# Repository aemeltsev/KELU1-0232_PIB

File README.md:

# KELU1-0232_PIB

![PCB image][KELU1-0232_PIB]

[KELU1-0232_PIB]:https://raw.githubusercontent.com/aemeltsev/KELU1-0232_PIB/master/hw/KELU1-0232_PCB.png

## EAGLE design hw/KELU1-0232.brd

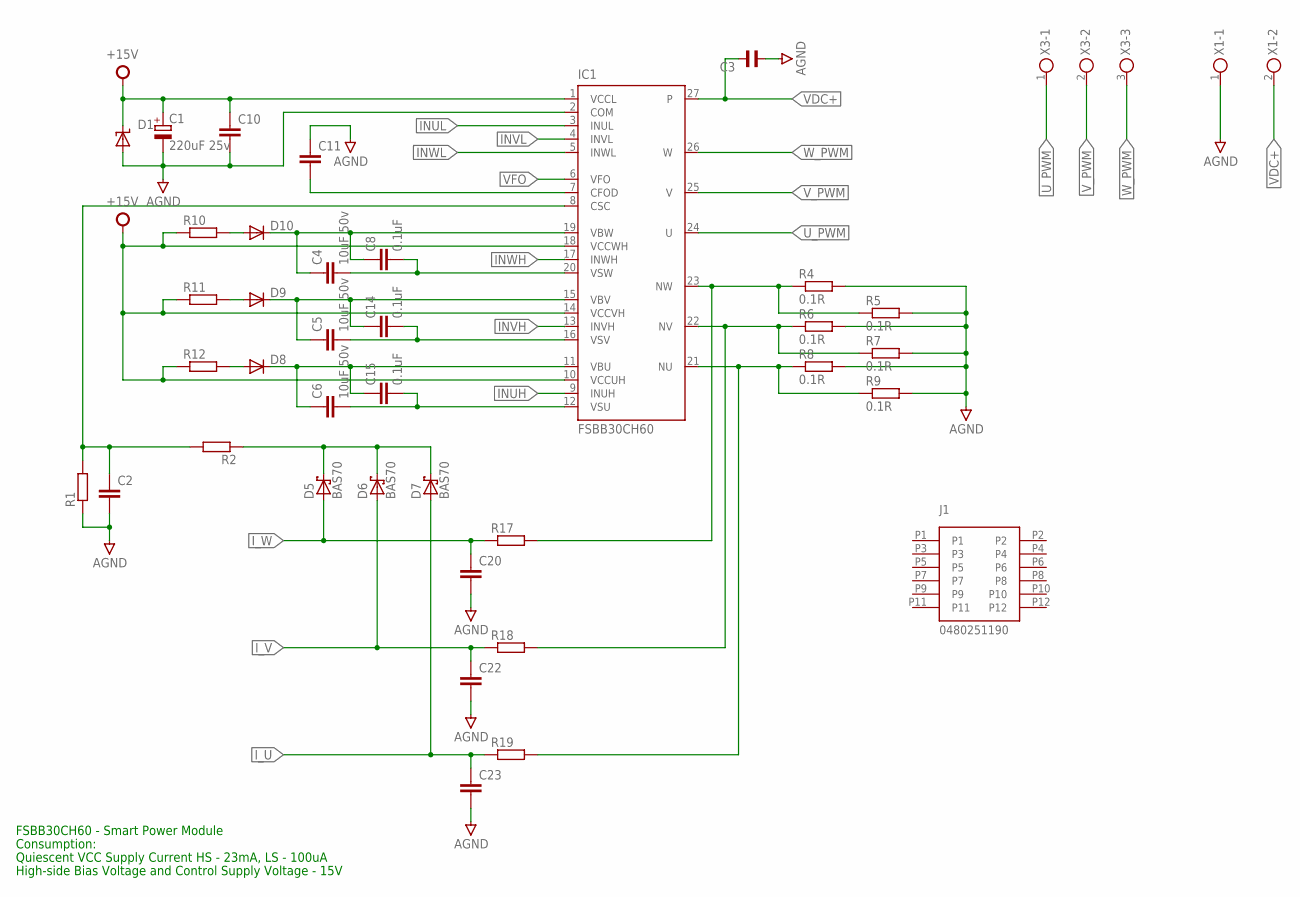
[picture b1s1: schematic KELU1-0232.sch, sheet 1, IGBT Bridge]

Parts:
C1: 220uF 25v; 140CLH-1010
C2, C10, C11, C20, C22, C23: C-EUC0603; C0603
C3: C-EU150-091X182; C150-091X182
C4, C5, C6: 10uF 50v; C1210K
C8, C14, C15: 0.1uF; C0805
D1: SUPPRESSOR-SMBJ; SMBJ
D5, D6, D7: BAS70; SOT23
D8, D9, D10: DIODE-MELF-MLL41; MELF-MLL41
IC1: FSBB30CH60
J1: 0480251190; JACK
R1, R2, R17, R18, R19: R-EU_R0603; R0603
R4, R5, R6, R7, R8, R9: 0.1R; R2512
R10, R11, R12: R-EU_R1206; R1206
X1: DG129-7.5-02P; DG129-7.5-02P-14-00A
X3: DG129-7.5-03P; DG129-7.5-03P-14-00A

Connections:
+15V: C1.+, C10.1, D1.C, IC1.1 (VCCL), IC1.10 (VCCUH), IC1.14 (VCCVH), IC1.18 (VCCWH), R10.1, R11.1, R12.1; also elsewhere on the board
AGND: C1.-, C2.2, C3.2, C10.2, C11.1, C20.2, C22.2, C23.2, D1.A, IC1.2 (COM), R1.1, R4.2, R5.2, R6.2, R7.2, R8.2, R9.2, X1.1; also elsewhere on the board
INUH: IC1.9 (INUH); also elsewhere on the board
INUL: IC1.3 (INUL); also elsewhere on the board
INVH: IC1.13 (INVH); also elsewhere on the board
INVL: IC1.4 (INVL); also elsewhere on the board
INWH: IC1.17 (INWH); also elsewhere on the board
INWL: IC1.5 (INWL); also elsewhere on the board
I_U: C23.1, D7.1 (A), R19.1; also elsewhere on the board
I_V: C22.1, D6.1 (A), R18.1; also elsewhere on the board
I_W: C20.1, D5.1 (A), R17.1; also elsewhere on the board
unnamed: D8.A, R12.2
unnamed: D9.A, R11.2
unnamed: C11.2, IC1.7 (CFOD)
unnamed: D10.A, R10.2
unnamed: C4.1, C8.1, D10.C, IC1.19 (VBW)
unnamed: C5.1, C14.1, D9.C, IC1.15 (VBV)
unnamed: C6.1, C15.1, D8.C, IC1.11 (VBU)
unnamed: C5.2, C14.2, IC1.16 (VSV)
unnamed: C6.2, C15.2, IC1.12 (VSU)
unnamed: C4.2, C8.2, IC1.20 (VSW)
unnamed: IC1.23 (NW), R4.1, R5.1, R17.2
unnamed: IC1.22 (NV), R6.1, R7.1, R18.2
unnamed: IC1.21 (NU), R8.1, R9.1, R19.2
unnamed: C2.1, IC1.8 (CSC), R1.2, R2.2
unnamed: D5.3 (C), D6.3 (C), D7.3 (C), R2.1
U_PWM: IC1.24 (U), X3.1
VDC+: C3.1, IC1.27, X1.2; also elsewhere on the board
VFO: IC1.6 (VFO); also elsewhere on the board
V_PWM: IC1.25 (V), X3.2
W_PWM: IC1.26 (W), X3.3

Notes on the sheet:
Consumption:
FSBB30CH60 - Smart Power Module
High-side Bias Voltage and Control Supply Voltage - 15V
Quiescent VCC Supply Current HS - 23mA, LS - 100uA

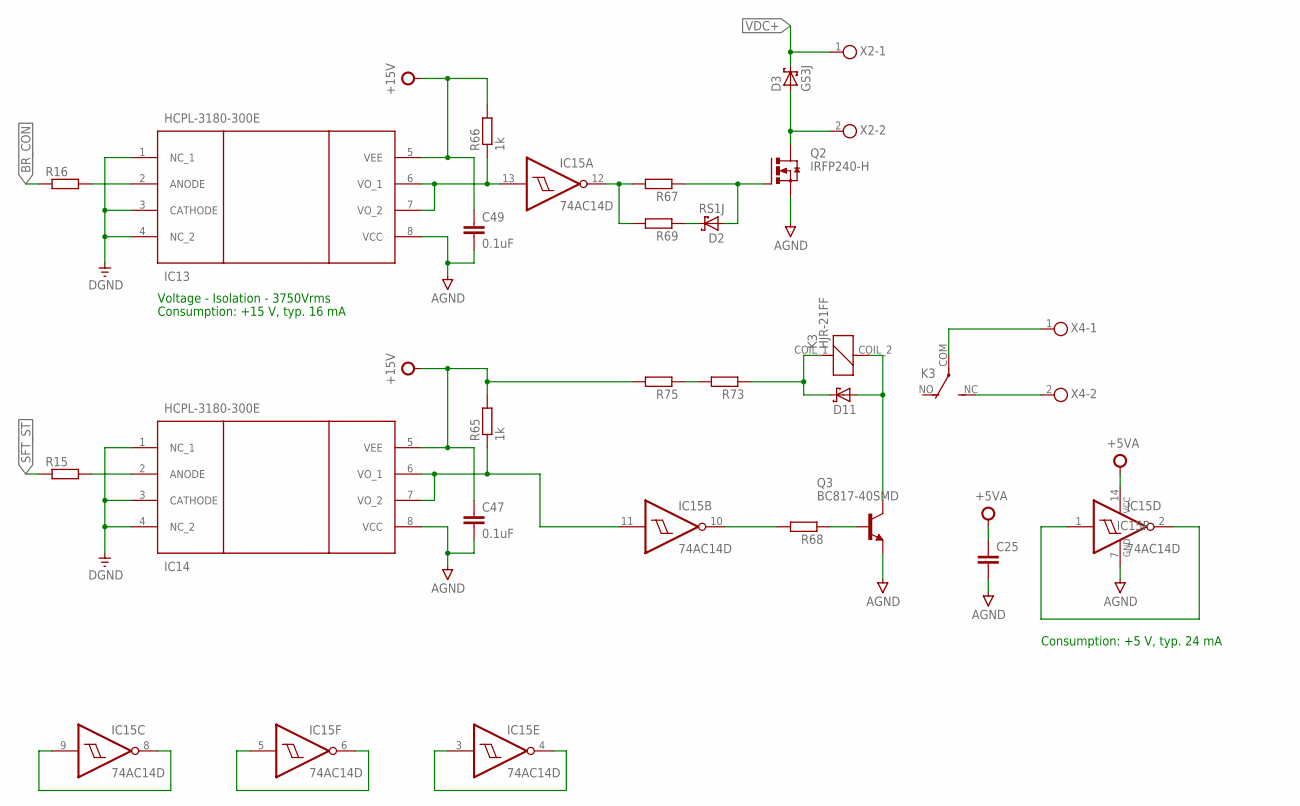
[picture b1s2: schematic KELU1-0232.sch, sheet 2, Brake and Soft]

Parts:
C25: C-EUC0603; C0603
C47, C49: 0.1uF; C1206
D2: RS1J; DIOM5326X292N
D3: GS3J; DIOM7959X265N
D11: SCHOTTKY_SMA; DIOM5326X292N
IC13, IC14: HCPL-3180-300E; HCPL-3180
IC15: 74AC14D; SO14
K3: HJR-21FF; HJR21FF
Q2: IRFP240-H; TO247BH
Q3: BC817-40SMD; SOT23-BEC
R15, R16: R-EU_R0603; R0603
R65, R66: 1k; M0805
R67, R68, R69, R73, R75: R-EU_M0805; M0805
X2, X4: DG129-7.5-02P; DG129-7.5-02P-14-00A

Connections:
+5VA: C25.1, IC15.14 (VCC); also elsewhere on the board
+15V: C47.1, C49.1, IC13.5 (VEE), IC14.5 (VEE), R65.2, R66.2, R75.2; also elsewhere on the board
AGND: C25.2, C47.2, C49.2, IC13.8 (VCC), IC14.8 (VCC), IC15.7 (GND), Q2.S, Q3.E; also elsewhere on the board
BR_CON: R16.1; also elsewhere on the board
DGND: IC13.1 (NC_1), IC13.3 (CATHODE), IC13.4 (NC_2), IC14.1 (NC_1), IC14.3 (CATHODE), IC14.4 (NC_2); also elsewhere on the board
unnamed: IC13.2 (ANODE), R16.2
unnamed: IC14.2 (ANODE), R15.2
unnamed: Q3.B, R68.1
unnamed: IC13.6 (VO_1), IC13.7 (VO_2), IC15.13 (I), R66.1
unnamed: IC15.12 (O), R67.2, R69.2
unnamed: IC14.6 (VO_1), IC14.7 (VO_2), IC15.11 (I), R65.1
unnamed: IC15.10 (O), R68.2
unnamed: D2.A, Q2.G, R67.1
unnamed: D2.K, R69.1
unnamed: K3.COM, X4.1
unnamed: K3.NC, X4.2
unnamed: D3.A, Q2.D, X2.2
unnamed: D11.K, K3.COIL_1, R73.1
unnamed: D11.A, K3.COIL_2, Q3.C
unnamed: R73.2, R75.1
unnamed: IC15.1 (I), IC15.2 (O)
unnamed: IC15.8 (O), IC15.9 (I)
unnamed: IC15.5 (I), IC15.6 (O)
unnamed: IC15.3 (I), IC15.4 (O)
SFT_ST: R15.1; also elsewhere on the board
VDC+: D3.K, X2.1; also elsewhere on the board

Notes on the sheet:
Consumption: +15 V, typ. 16 mA
Consumption: +5 V, typ. 24 mA
Voltage - Isolation - 3750Vrms

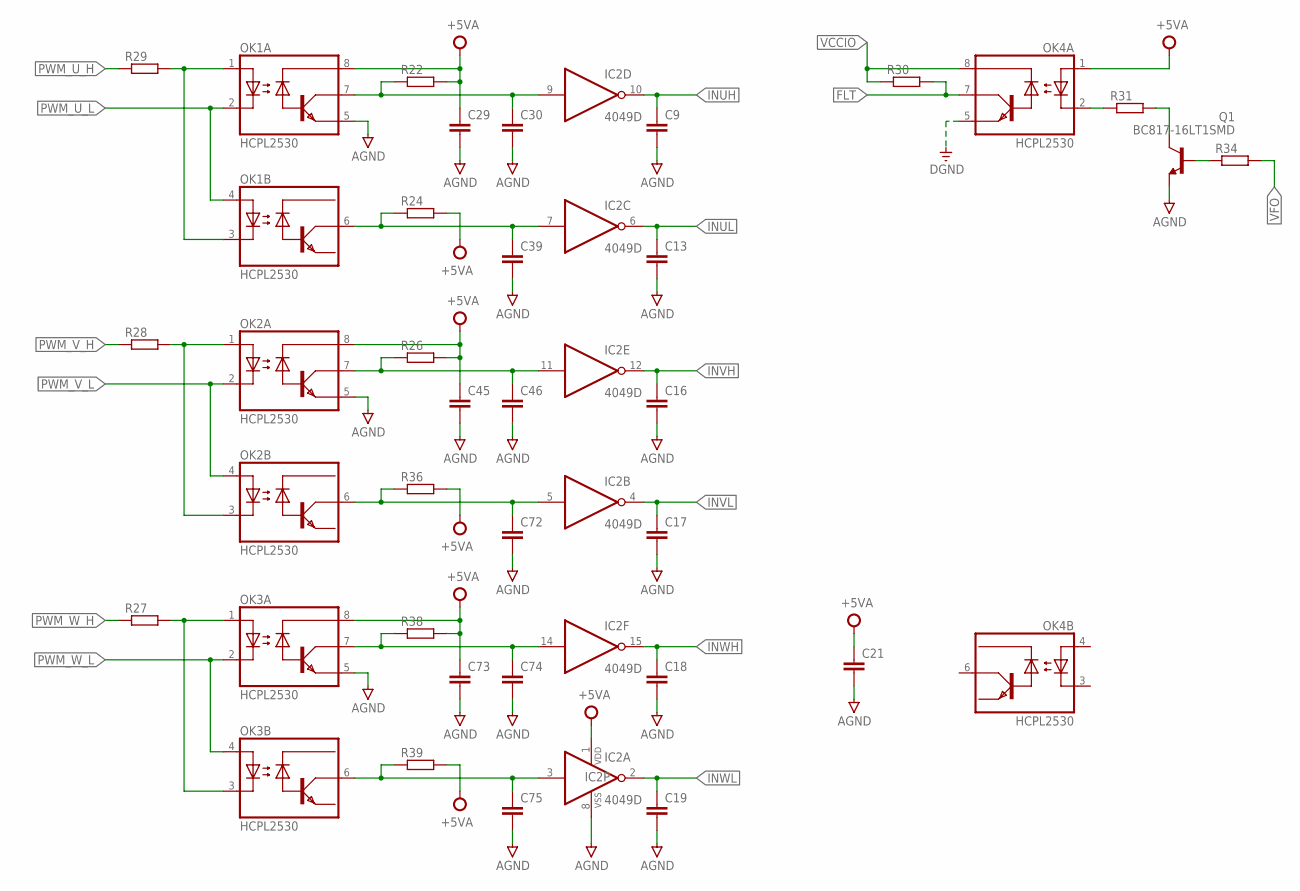
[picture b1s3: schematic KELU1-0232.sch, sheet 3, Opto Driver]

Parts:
C9, C13, C16, C17, C18, C19, C21, C29, C30, C39, C45, C46, C72, C73, C74, C75: C-EUC0603; C0603
IC2: 4049D; SO16
OK1, OK2, OK3, OK4: HCPL2530; DIL08
Q1: BC817-16LT1SMD; SOT23-BEC
R22, R24, R26, R27, R28, R29, R30, R31, R34, R36, R38, R39: R-EU_R0603; R0603

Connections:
+5VA: C21.1, C29.1, C45.1, C73.1, IC2.1 (VDD), OK1.8 (VCC), OK2.8 (VCC), OK3.8 (VCC), OK4.1 (A1), R22.2, R24.2, R26.2, R36.2, R38.2, R39.2; also elsewhere on the board
AGND: C9.2, C13.2, C16.2, C17.2, C18.2, C19.2, C21.2, C29.2, C30.2, C39.2, C45.2, C46.2, C72.2, C73.2, C74.2, C75.2, IC2.8 (VSS), OK1.5 (GND), OK2.5 (GND), OK3.5 (GND), Q1.E; also elsewhere on the board
DGND: OK4.5 (GND); also elsewhere on the board
FLT: OK4.7 (VO1), R30.2; also elsewhere on the board
INUH: C9.1, IC2.10 (O); also elsewhere on the board
INUL: C13.1, IC2.6 (O); also elsewhere on the board
INVH: C16.1, IC2.12 (O); also elsewhere on the board
INVL: C17.1, IC2.4 (O); also elsewhere on the board
INWH: C18.1, IC2.15 (O); also elsewhere on the board
INWL: C19.1, IC2.2 (O); also elsewhere on the board
unnamed: C30.1, IC2.9 (I), OK1.7 (VO1), R22.1
unnamed: C39.1, IC2.7 (I), OK1.6 (VO2), R24.1
unnamed: OK1.1 (A1), OK1.3 (C2), R29.2
unnamed: C46.1, IC2.11 (I), OK2.7 (VO1), R26.1
unnamed: C72.1, IC2.5 (I), OK2.6 (VO2), R36.1
unnamed: OK2.1 (A1), OK2.3 (C2), R28.2
unnamed: C74.1, IC2.14 (I), OK3.7 (VO1), R38.1
unnamed: OK4.2 (C1), R31.1
unnamed: C75.1, IC2.3 (I), OK3.6 (VO2), R39.1
unnamed: OK3.1 (A1), OK3.3 (C2), R27.2
unnamed: Q1.C, R31.2
unnamed: Q1.B, R34.1
PWM_U_H: R29.1; also elsewhere on the board
PWM_U_L: OK1.2 (C1), OK1.4 (A2); also elsewhere on the board
PWM_V_H: R28.1; also elsewhere on the board
PWM_V_L: OK2.2 (C1), OK2.4 (A2); also elsewhere on the board
PWM_W_H: R27.1; also elsewhere on the board
PWM_W_L: OK3.2 (C1), OK3.4 (A2); also elsewhere on the board
VCCIO: OK4.8 (VCC), R30.1; also elsewhere on the board
VFO: R34.2; also elsewhere on the board

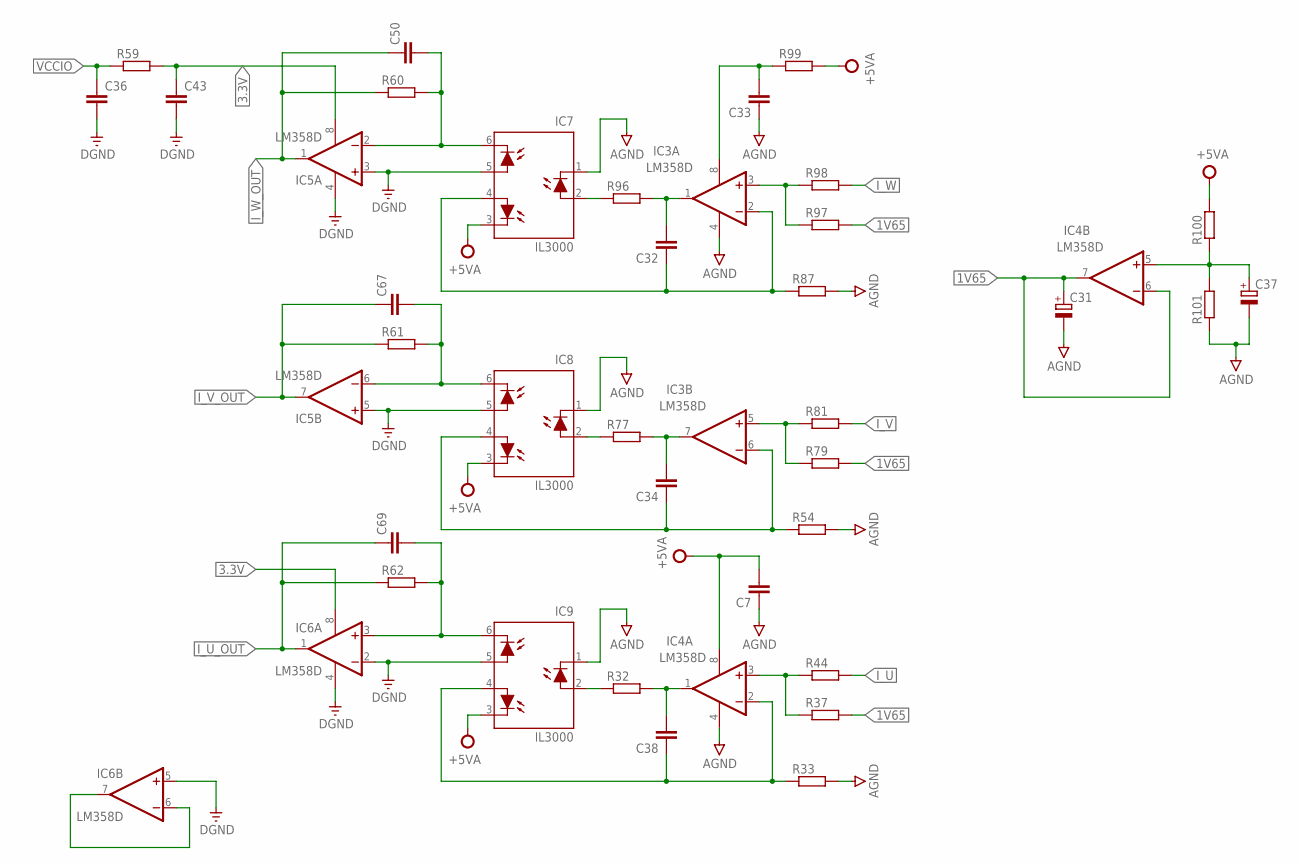
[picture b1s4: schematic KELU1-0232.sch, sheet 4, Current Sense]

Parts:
C7, C32, C33, C34, C36, C38, C43, C50, C67, C69: C-EUC0603; C0603
C31, C37: CPOL-EUSMCB; SMC_B
IC3, IC4, IC5, IC6: LM358D; SO08
IC7, IC8, IC9: IL3000; DIL08-400
R32, R33, R37, R44, R54, R59, R60, R61, R62, R77, R79, R81, R87, R96, R97, R98, R99, R100, R101: R-EU_R0603; R0603

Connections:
1V65: C31.+, IC4.6 (-IN), IC4.7 (OUT), R37.2, R79.2, R97.2
3.3V: C43.1, IC5.8 (V+), IC6.8 (V+), R59.2
5VA: C33.2, IC3.8 (V+), R99.1
+5VA: C7.2, IC4.8 (V+), IC7.3 (C3), IC8.3 (C3), IC9.3 (C3), R99.2, R100.2; also elsewhere on the board
AGND: C7.1, C31.-, C33.1, C37.-, IC3.4 (V-), IC4.4 (V-), IC7.1 (C1), IC8.1 (C1), IC9.1 (C1), R33.2, R54.2, R87.2, R101.1; also elsewhere on the board
DGND: C36.2, C43.2, IC5.3 (+IN), IC5.4 (V-), IC5.5 (+IN), IC6.2 (-IN), IC6.4 (V-), IC6.5 (+IN), IC7.5 (A5), IC8.5 (A5), IC9.5 (A5); also elsewhere on the board
I_U: R44.2; also elsewhere on the board
I_U_OUT: C69.1, IC6.1 (OUT), R62.1; also elsewhere on the board
I_V: R81.2; also elsewhere on the board
I_V_OUT: C67.1, IC5.7 (OUT), R61.1; also elsewhere on the board
I_W: R98.2; also elsewhere on the board
I_W_OUT: C50.1, IC5.1 (OUT), R60.1; also elsewhere on the board
unnamed: C32.2, IC3.1 (OUT), R96.2
unnamed: IC7.2 (A2), R96.1
unnamed: IC3.3 (+IN), R97.1, R98.1
unnamed: C37.+, IC4.5 (+IN), R100.1, R101.2
unnamed: C50.2, IC5.2 (-IN), IC7.6 (C6), R60.2
unnamed: C32.1, IC3.2 (-IN), IC7.4 (A4), R87.1
unnamed: IC8.2 (A2), R77.1
unnamed: C34.2, IC3.7 (OUT), R77.2
unnamed: C34.1, IC3.6 (-IN), IC8.4 (A4), R54.1
unnamed: C67.2, IC5.6 (-IN), IC8.6 (C6), R61.2
unnamed: C69.2, IC6.3 (+IN), IC9.6 (C6), R62.2
unnamed: IC9.2 (A2), R32.1
unnamed: IC3.5 (+IN), R79.1, R81.1
unnamed: C38.2, IC4.1 (OUT), R32.2
unnamed: IC6.6 (-IN), IC6.7 (OUT)
unnamed: C38.1, IC4.2 (-IN), IC9.4 (A4), R33.1
unnamed: IC4.3 (+IN), R37.1, R44.1
VCCIO: C36.1, R59.1; also elsewhere on the board

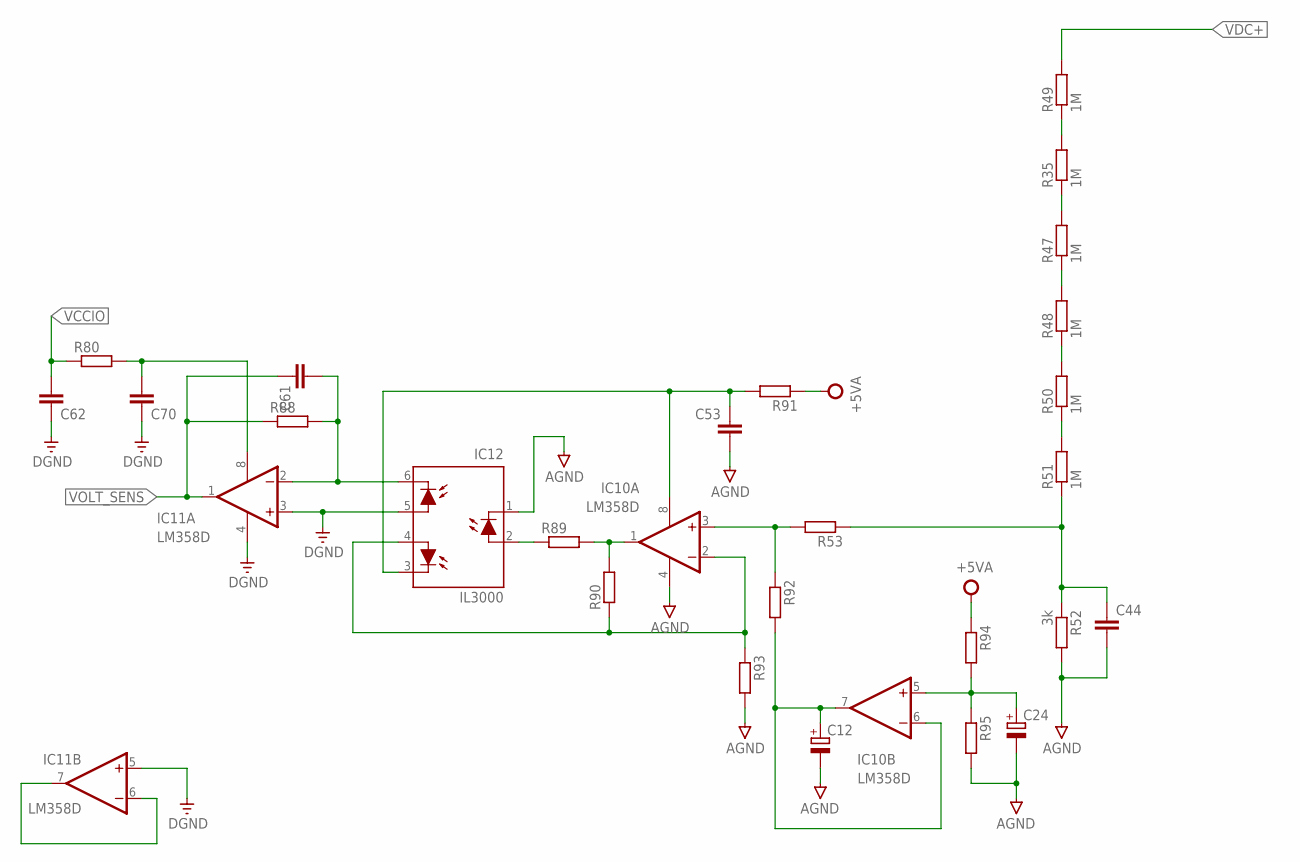
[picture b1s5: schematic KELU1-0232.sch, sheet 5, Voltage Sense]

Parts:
C12, C24: CPOL-EUSMCB; SMC_B
C44: C-EUC1206; C1206
C53, C61, C62, C70: C-EUC0603; C0603
IC10, IC11: LM358D; SO08
IC12: IL3000; DIL08-400
R35, R47, R48, R49, R50, R51: 1M; M1206
R52: 3k; M1206
R53, R80, R88, R89, R90, R91, R92, R93, R94, R95: R-EU_R0603; R0603

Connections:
+5VA: R91.1, R94.1; also elsewhere on the board
AGND: C12.-, C24.-, C44.2, C53.2, IC10.4 (V-), IC12.1 (C1), R52.2, R93.2, R95.2; also elsewhere on the board
DGND: C62.1, C70.1, IC11.3 (+IN), IC11.4 (V-), IC11.5 (+IN), IC12.5 (A5); also elsewhere on the board
unnamed: R50.1, R51.2
unnamed: R48.1, R50.2
unnamed: R47.1, R48.2
unnamed: R35.1, R47.2
unnamed: R35.2, R49.1
unnamed: IC10.3 (+IN), R53.2, R92.1
unnamed: C44.1, R51.1, R52.1, R53.1
unnamed: IC12.2 (A2), R89.1
unnamed: IC10.1 (OUT), R89.2, R90.2
unnamed: IC10.2 (-IN), IC12.4 (A4), R90.1, R93.1
unnamed: C12.+, IC10.6 (-IN), IC10.7 (OUT), R92.2
unnamed: C61.2, IC11.2 (-IN), IC12.6 (C6), R88.2
unnamed: C53.1, IC10.8 (V+), IC12.3 (C3), R91.2
unnamed: C70.2, IC11.8 (V+), R80.2
unnamed: C24.+, IC10.5 (+IN), R94.2, R95.1
unnamed: IC11.6 (-IN), IC11.7 (OUT)
VCCIO: C62.2, R80.1; also elsewhere on the board
VDC+: R49.2; also elsewhere on the board
VOLT_SENS: C61.1, IC11.1 (OUT), R88.1; also elsewhere on the board

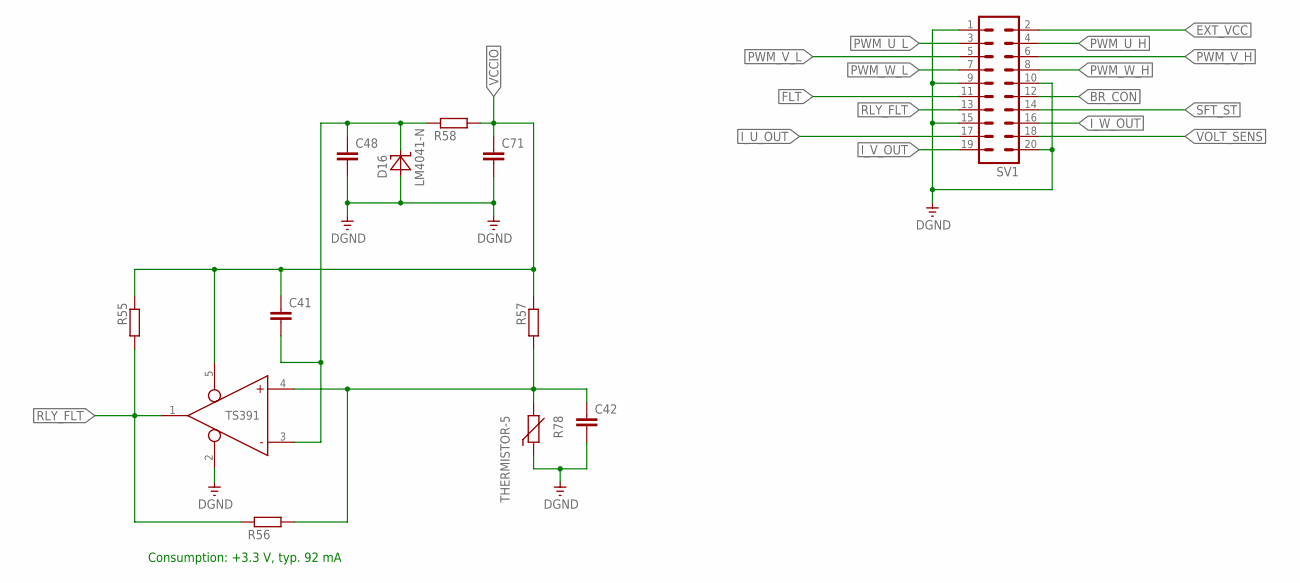
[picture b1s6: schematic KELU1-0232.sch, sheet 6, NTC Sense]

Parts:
C41, C42, C48, C71: C-EUC0603; C0603
D16: LM4041-N; SOT23
R55, R56, R57, R58: R-EU_R0603; R0603
R78: THERMISTOR-5; R-5
SV1: ML20
U$2: TS391; SOT23-5

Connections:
BR_CON: SV1.12; also elsewhere on the board
DGND: C42.2, C48.2, C71.2, D16.2 (C), R78.1, SV1.1, SV1.9, SV1.10, SV1.15, SV1.20, U$2.2 (GND); also elsewhere on the board
EXT_VCC: SV1.2; also elsewhere on the board
FLT: SV1.11; also elsewhere on the board
I_U_OUT: SV1.17; also elsewhere on the board
I_V_OUT: SV1.19; also elsewhere on the board
I_W_OUT: SV1.16; also elsewhere on the board
unnamed: C42.1, R56.2, R57.2, R78.2, U$2.4 (IN+)
unnamed: C41.2, C48.1, D16.1 (A), R58.1, U$2.3 (IN-)
PWM_U_H: SV1.4; also elsewhere on the board
PWM_U_L: SV1.3; also elsewhere on the board
PWM_V_H: SV1.6; also elsewhere on the board
PWM_V_L: SV1.5; also elsewhere on the board
PWM_W_H: SV1.8; also elsewhere on the board
PWM_W_L: SV1.7; also elsewhere on the board
RLY_FLT: R55.2, R56.1, SV1.13, U$2.1 (OUT)
SFT_ST: SV1.14; also elsewhere on the board
VCCIO: C41.1, C71.1, R55.1, R57.1, R58.2, U$2.5 (VCC); also elsewhere on the board
VOLT_SENS: SV1.18; also elsewhere on the board

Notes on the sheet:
Consumption: +3.3 V, typ. 92 mA

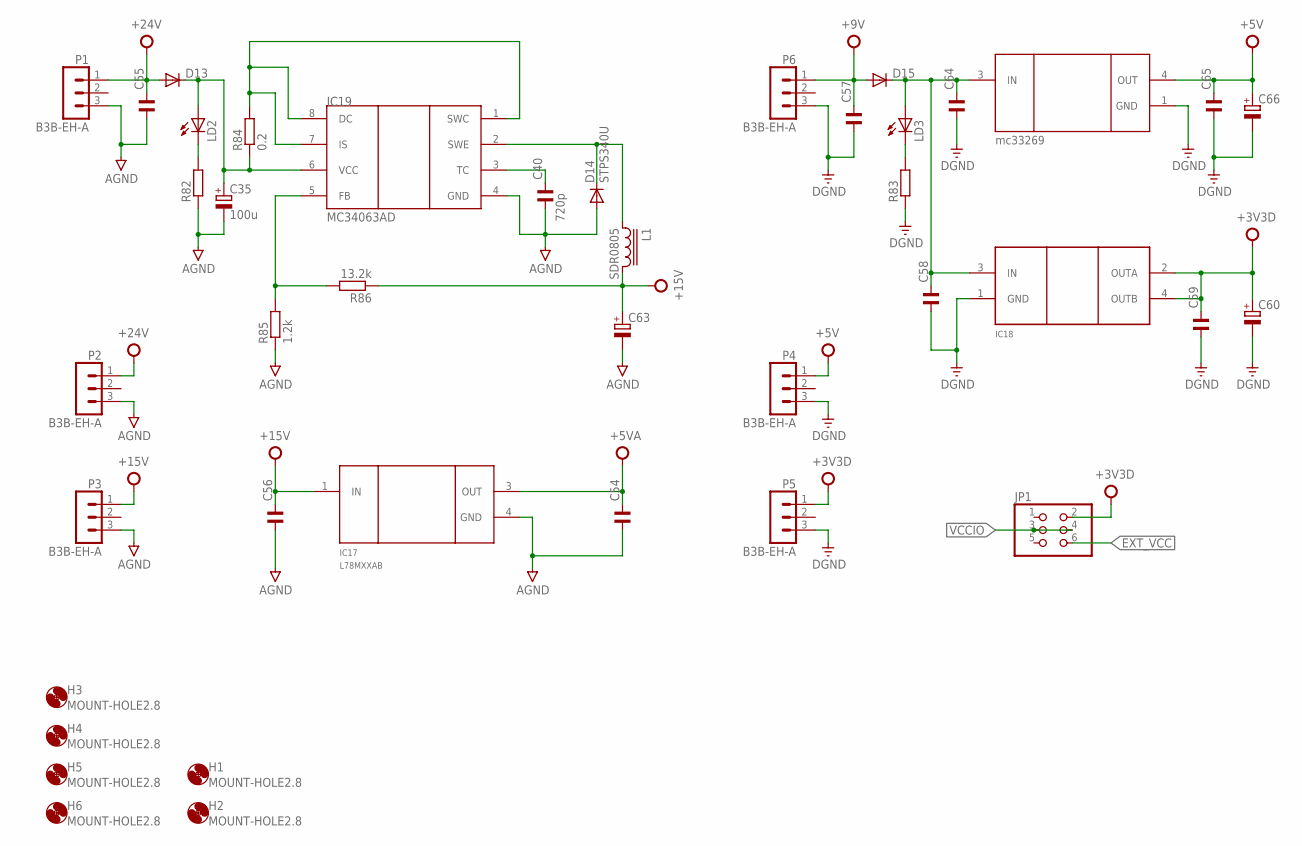
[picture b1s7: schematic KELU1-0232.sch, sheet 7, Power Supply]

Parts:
C35: 100u; 175TMP-0810
C40: 720p; C0805
C54, C55, C56, C57, C58, C59, C64, C65: C-EUC0805; C0805
C60, C66: CPOL-EUA/3216-18R; A/3216-18R
C63: CPOL-EU175TMP-0810; 175TMP-0810
D13, D15: DIODE-SMB; SMB
D14: STPS340U; SMB
H1, H2, H3, H4, H5, H6: MOUNT-HOLE2.8; 2,8
IC17: L78MXXAB; D-PAK_TO252AA
IC18: LM1117; SOT223
IC19: MC34063AD; SOIC8
JP1: PINHD-2X3; 2X03
L1: SDR0805
LD2, LD3: LEDCHIPLED_0805; CHIPLED_0805
P1, P2, P3, P4, P5, P6: B3B-EH-A
R82, R83: R-EU_M0805; M0805
R84: 0.2; R2512
R85: 1.2k; M0805
R86: 13.2k; M0805
U$1: MC33269DPAK; D-PAK_TO252AA

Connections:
+3V3D: C59.1, C60.+, IC18.2 (OUTA), IC18.4 (OUTB), JP1.2, P5.1
+5V: C65.1, C66.+, P4.1, U$1.4 (OUT)
+5VA: C54.1, IC17.3 (OUT); also elsewhere on the board
+9V: C57.1, D15.A, P6.1
+15V: C56.1, C63.+, IC17.1 (IN), L1.2, P3.1, R86.1; also elsewhere on the board
+24V: C55.1, D13.A, P1.1, P2.1
AGND: C35.-, C40.2, C54.2, C55.2, C56.2, C63.-, D14.A, IC17.4 (GND), IC19.4 (GND), P1.3, P2.3, P3.3, R82.1, R85.1; also elsewhere on the board
DGND: C57.2, C58.2, C59.2, C60.-, C64.2, C65.2, C66.-, IC18.1 (GND), P4.3, P5.3, P6.3, R83.1, U$1.1 (GND); also elsewhere on the board
EXT_VCC: JP1.6; also elsewhere on the board
unnamed: LD2.C, R82.2
unnamed: LD3.C, R83.2
unnamed: IC19.1 (SWC), IC19.7 (IS), IC19.8 (DC), R84.2
unnamed: IC19.5 (FB), R85.2, R86.2
unnamed: C40.1, IC19.3 (TC)
unnamed: C58.1, C64.1, D15.C, IC18.3 (IN), LD3.A, U$1.3 (IN)
unnamed: D14.C, IC19.2 (SWE), L1.1
unnamed: C35.+, D13.C, IC19.6 (VCC), LD2.A, R84.1
VCCIO: JP1.3, JP1.4; also elsewhere on the board

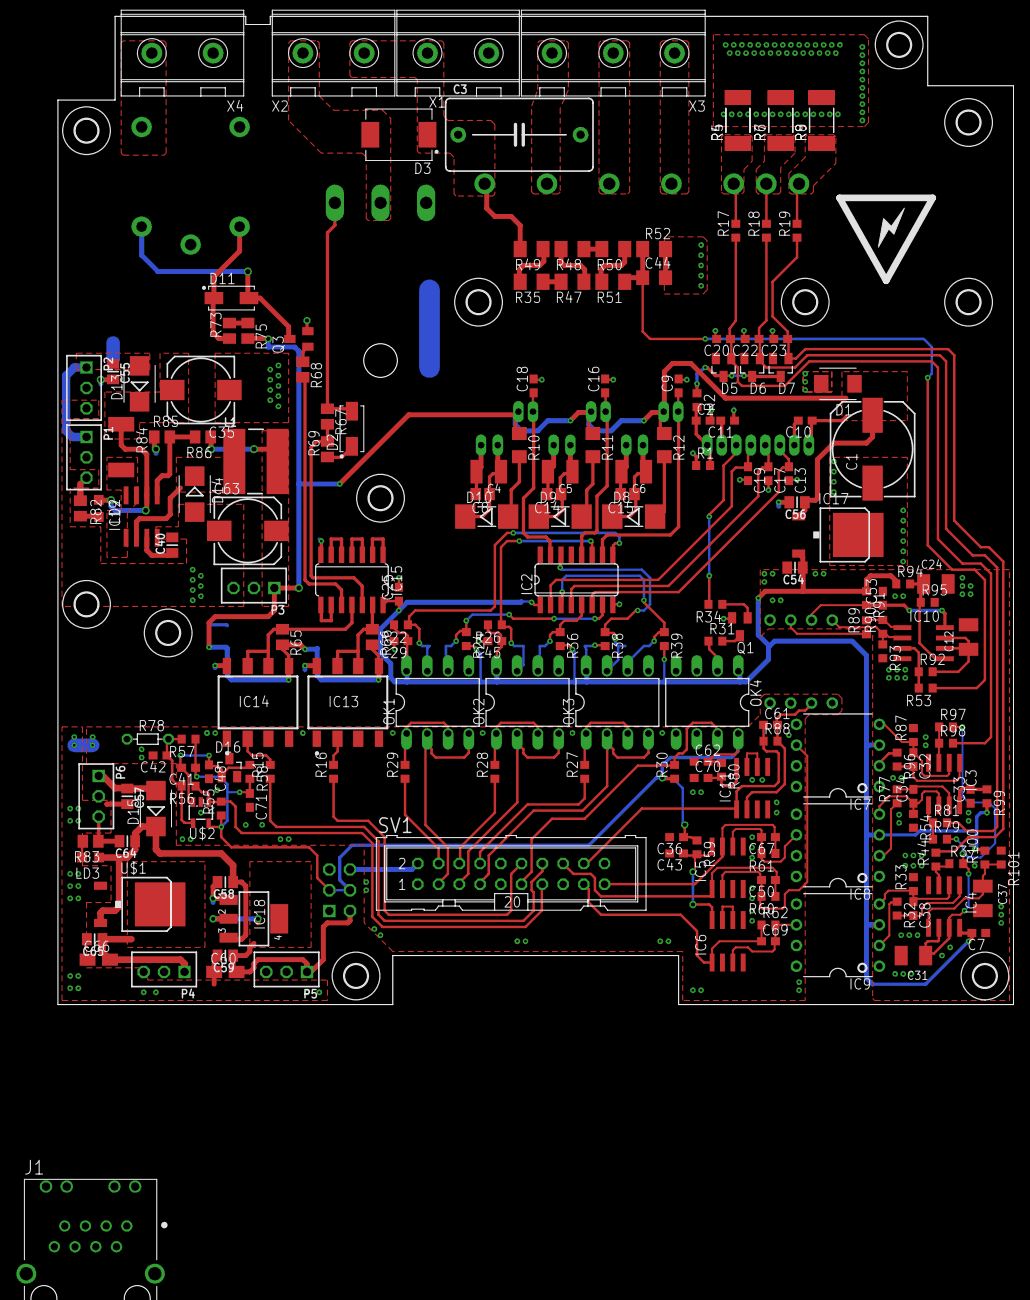
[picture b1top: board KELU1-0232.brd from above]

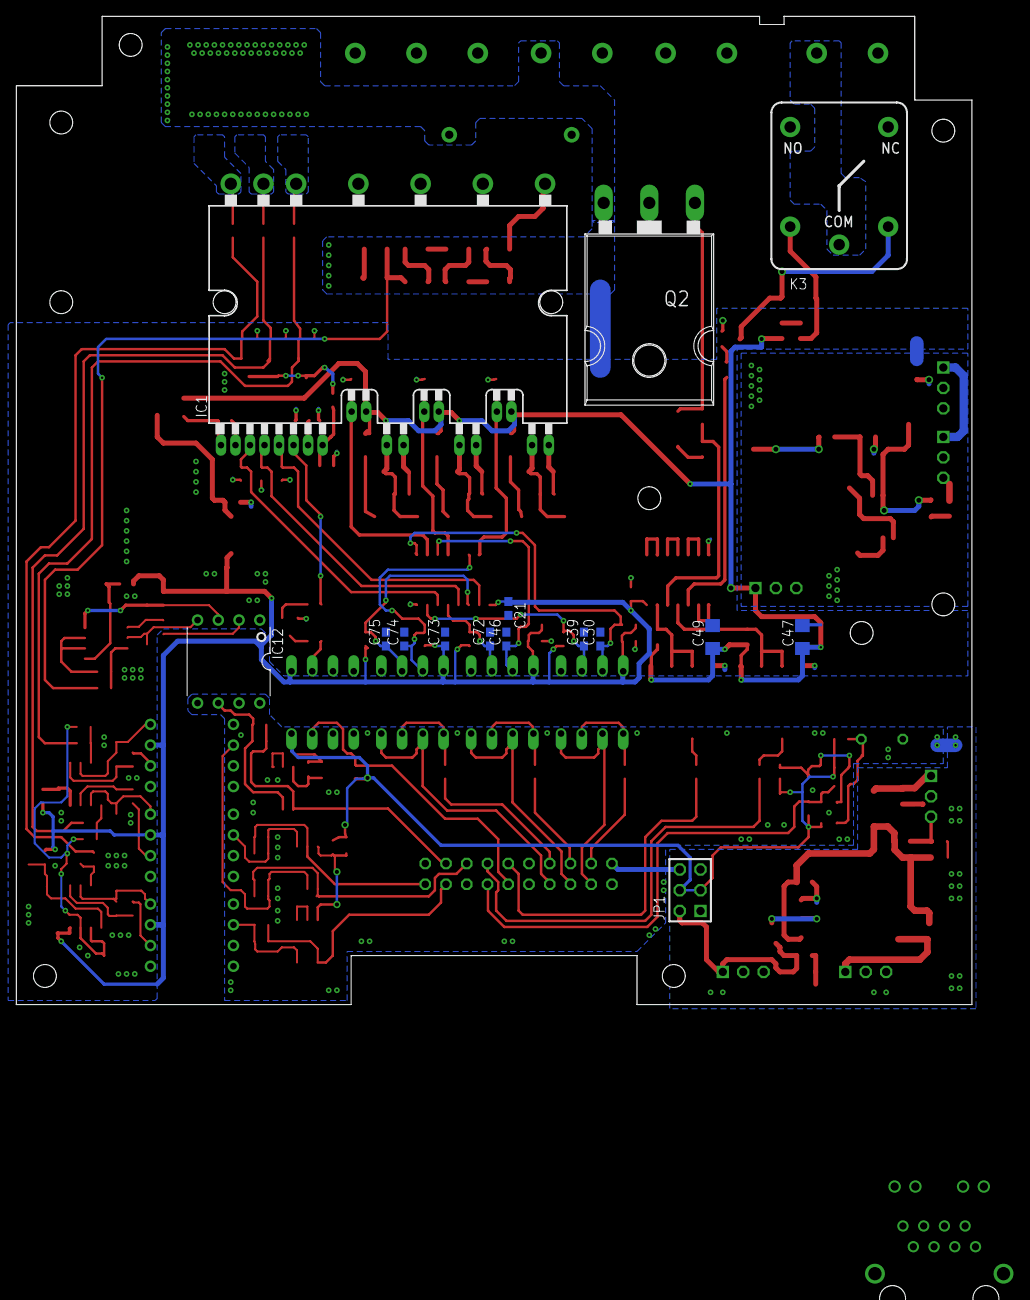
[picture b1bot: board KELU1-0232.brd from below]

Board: 2 copper layers, 117.0 x 121.0 mm, 220 parts (15 on the bottom side), 130 nets.

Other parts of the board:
H7, H8, H9, H10, H11: MOUNT-HOLE2.8; 2,8
U$3: ICON_BOLT-L

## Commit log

2019-01-23 Add files
    Add example files
2019-01-23 Update README.md
    Add image pcb
2019-01-29 Add files
    Add project and image file
2020-03-10 refresh
    refresh

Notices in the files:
parts and their libraries:
inductor-bourns: Copyright (C) 2008, Bob Starr
con-jst-eh: Copyright (C) 2016, Bob Starr
dicons: Copyright (C) 2004, Bob Starr (rtzaudio@mindspring.com)
